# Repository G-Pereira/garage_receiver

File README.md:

# Garage Receiver
A home made receiver to replace a broken one

## CADLAB View

View this project on [CADLAB.io](https://cadlab.io/project/1891). 

## How it works

This board works with 24V AC power supply and reponds to an RF signal which makes the input CT+ and CT- connect to each other and that makes the door open or close. The RF receiver is not included since they are readily available and some of you would need 443MHz and others 315MHz to interface with existing hardware.
You can use your existing remote by configuring the code with the switches.

## New features

In case you need more features feel free to ask for additions to the board! (Or make a pull request)

## License

Make sure to check the [License](LICENSE) file for information regarding the contents of this repository.

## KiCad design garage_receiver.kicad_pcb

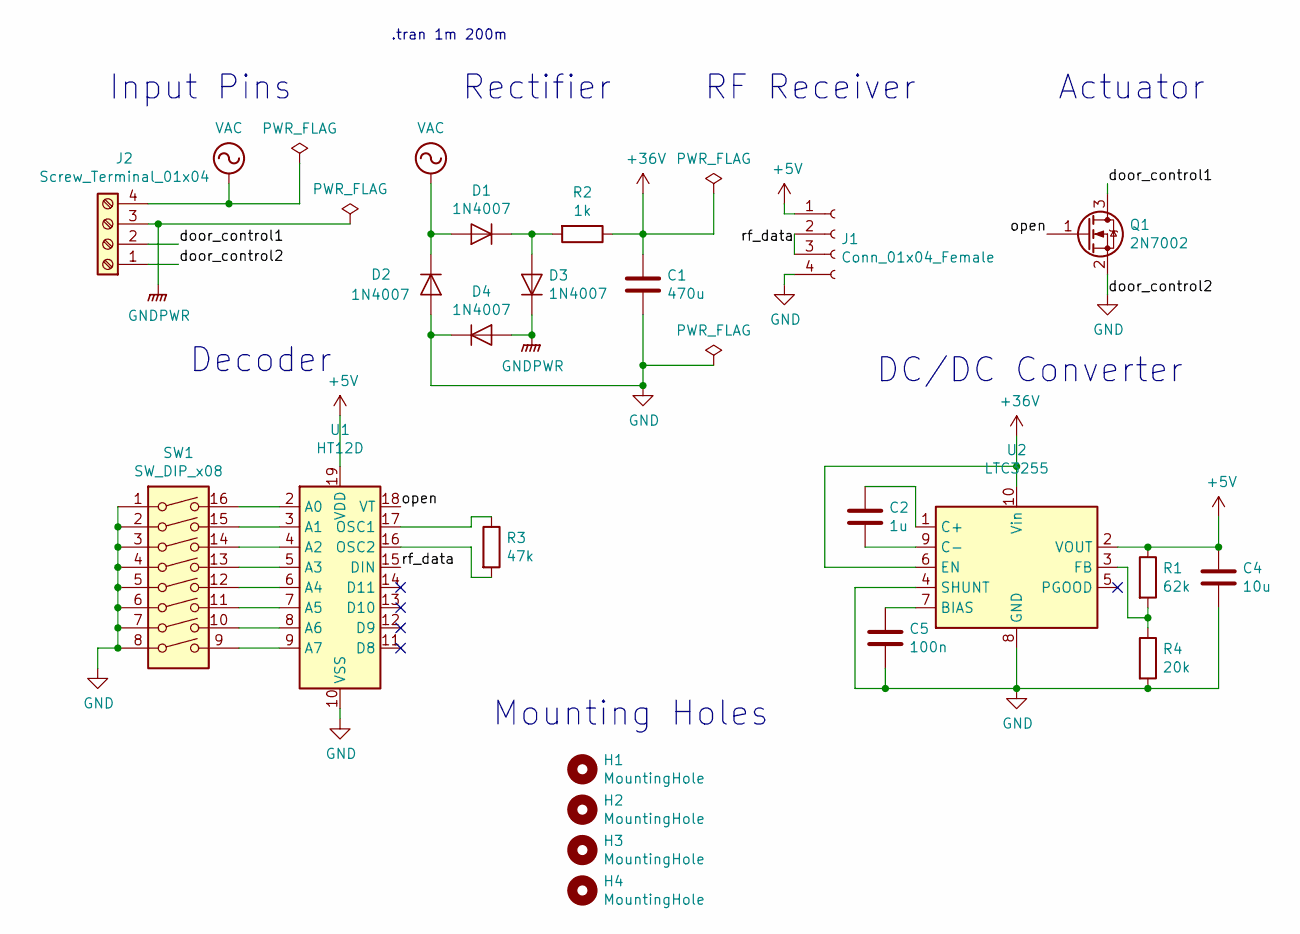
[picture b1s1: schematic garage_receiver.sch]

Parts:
C1: 470u; CP_Radial_D10.0mm_P5.00mm
C2: 1u; C_0805_2012Metric
C4: 10u; C_0805_2012Metric
C5: 100n; C_0805_2012Metric
D1, D2, D3, D4: 1N4007; D_DO-41_SOD81_P10.16mm_Horizontal
H1, H2, H3, H4: MountingHole; MountingHole_3.2mm_M3_Pad_Via
J1: Conn_01x04_Female; PinSocket_1x04_P2.54mm_Vertical
J2: Screw_Terminal_01x04; TerminalBlock_RND_205-00003_1x04_P5.00mm_Horizontal
Q1: 2N7002; SOT-23
R1: 62k; R_0805_2012Metric
R2: 1k; R_0805_2012Metric
R3: 47k; R_0805_2012Metric
R4: 20k; R_0805_2012Metric
SW1: SW_DIP_x08; SW_DIP_SPSTx08_Slide_9.78x22.5mm_W7.62mm_P2.54mm
U1: HT12D; SOIC-20W_7.5x12.8mm_P1.27mm
U2: LTC3255; MSOP-10-1EP_3x3mm_P0.5mm_EP1.68x1.88mm_ThermalVias

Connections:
+5V: C4.1, J1.1, R1.1, U1.19 (VDD), U2.2 (VOUT)
+36V: C1.1, R2.1, U2.6 (EN), U2.10 (Vin)
/door_control1: J2.2, Q1.3 (D)
/open: Q1.1 (G), U1.18 (VT)
/rf_data: J1.2, J1.3, U1.15 (DIN)
GND: C1.2, C4.2, C5.2, D2.2 (A), D4.1 (K), J1.4, J2.1, Q1.2 (S), R4.2, SW1.1, SW1.2, SW1.3, SW1.4, SW1.5, SW1.6, SW1.7, SW1.8, U1.10 (VSS), U2.4 (SHUNT), U2.8 (GND), U2.11 (GND)
GNDPWR: D3.1 (K), D4.2 (A), J2.3
unnamed: C2.1, U2.1 (C+)
unnamed: C2.2, U2.9 (C-)
unnamed: C5.1, U2.7 (BIAS)
unnamed: D1.1 (K), D3.2 (A), R2.2
unnamed: R1.2, R4.1, U2.3 (FB)
unnamed: R3.1, U1.17 (OSC1)
unnamed: R3.2, U1.16 (OSC2)
unnamed: SW1.9, U1.9 (A7)
unnamed: SW1.10, U1.8 (A6)
unnamed: SW1.11, U1.7 (A5)
unnamed: SW1.12, U1.6 (A4)
unnamed: SW1.13, U1.5 (A3)
unnamed: SW1.14, U1.4 (A2)
unnamed: SW1.15, U1.3 (A1)
unnamed: SW1.16, U1.2 (A0)
VAC: D1.2 (A), D2.1 (K), J2.4

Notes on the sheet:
Rectifier
DC/DC Converter
Decoder
Input Pins
RF Receiver
Actuator
Mounting Holes
.tran 1m 200m

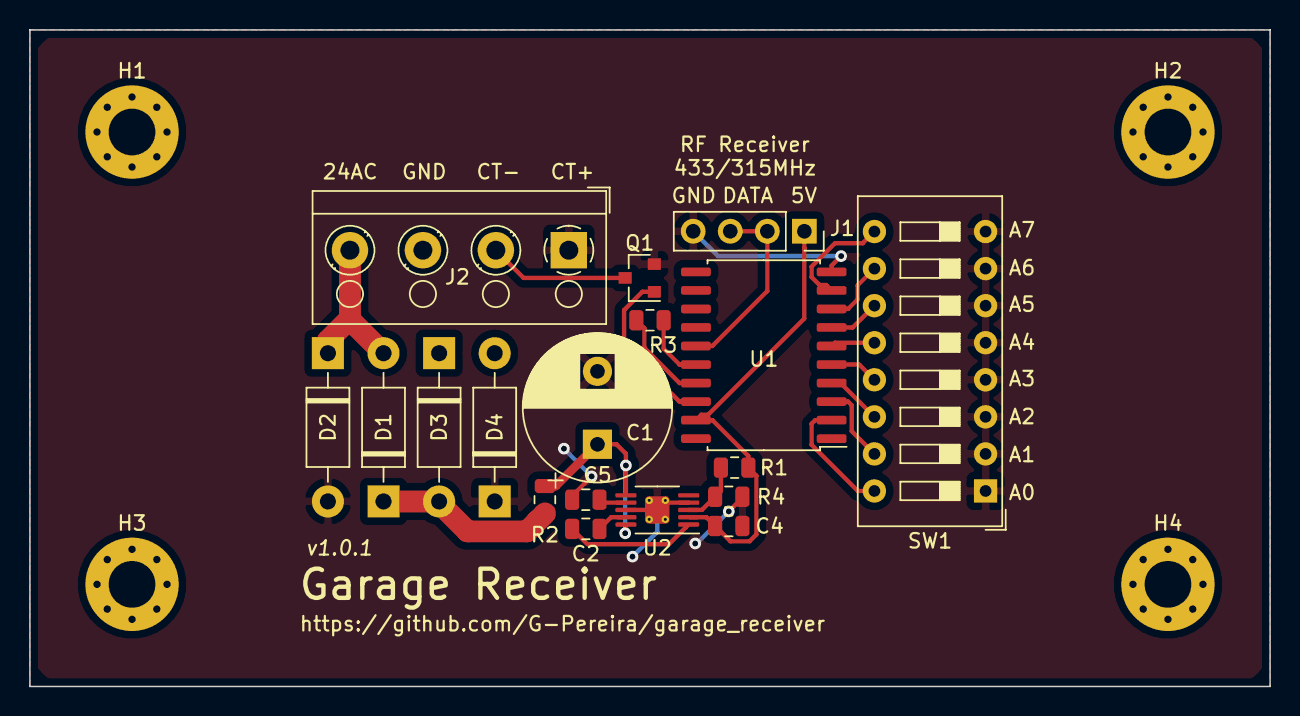
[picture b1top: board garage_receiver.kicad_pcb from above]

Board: 2 copper layers, 85.0 x 45.0 mm, 22 parts (0 on the bottom side), 23 nets.

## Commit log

2019-06-20 Backlink to CADLAB.io has been added.
2019-06-20 CADLAB needs *-cache.lib
2019-06-20 Project Initialization
2019-06-21 Schematic complete
2019-06-21 DC/DC Converter
2019-06-21 DC/DC Converter Controller
2019-06-21 PCB Layout
2019-06-21 Prepare for production
2019-06-21 Change Control Pin Labels
2019-06-21 Rotate Labels
2019-06-21 Remove Uneeded File
2019-06-21 Fix PCB files
2019-06-21 Fix Flipped Component
2019-06-23 DC/DC converter updated to input range 4V to 48V
2019-06-23 Label secret code switches and updated BOM
2019-06-23 Fixed Soldermask Clearance
2019-06-23 Ground Screw Holes
2019-06-29 Removed Undersized and Uneded SMD Capacitor
2019-06-29 Updated Image
2020-10-31 Add explicit ref to the License in the README
